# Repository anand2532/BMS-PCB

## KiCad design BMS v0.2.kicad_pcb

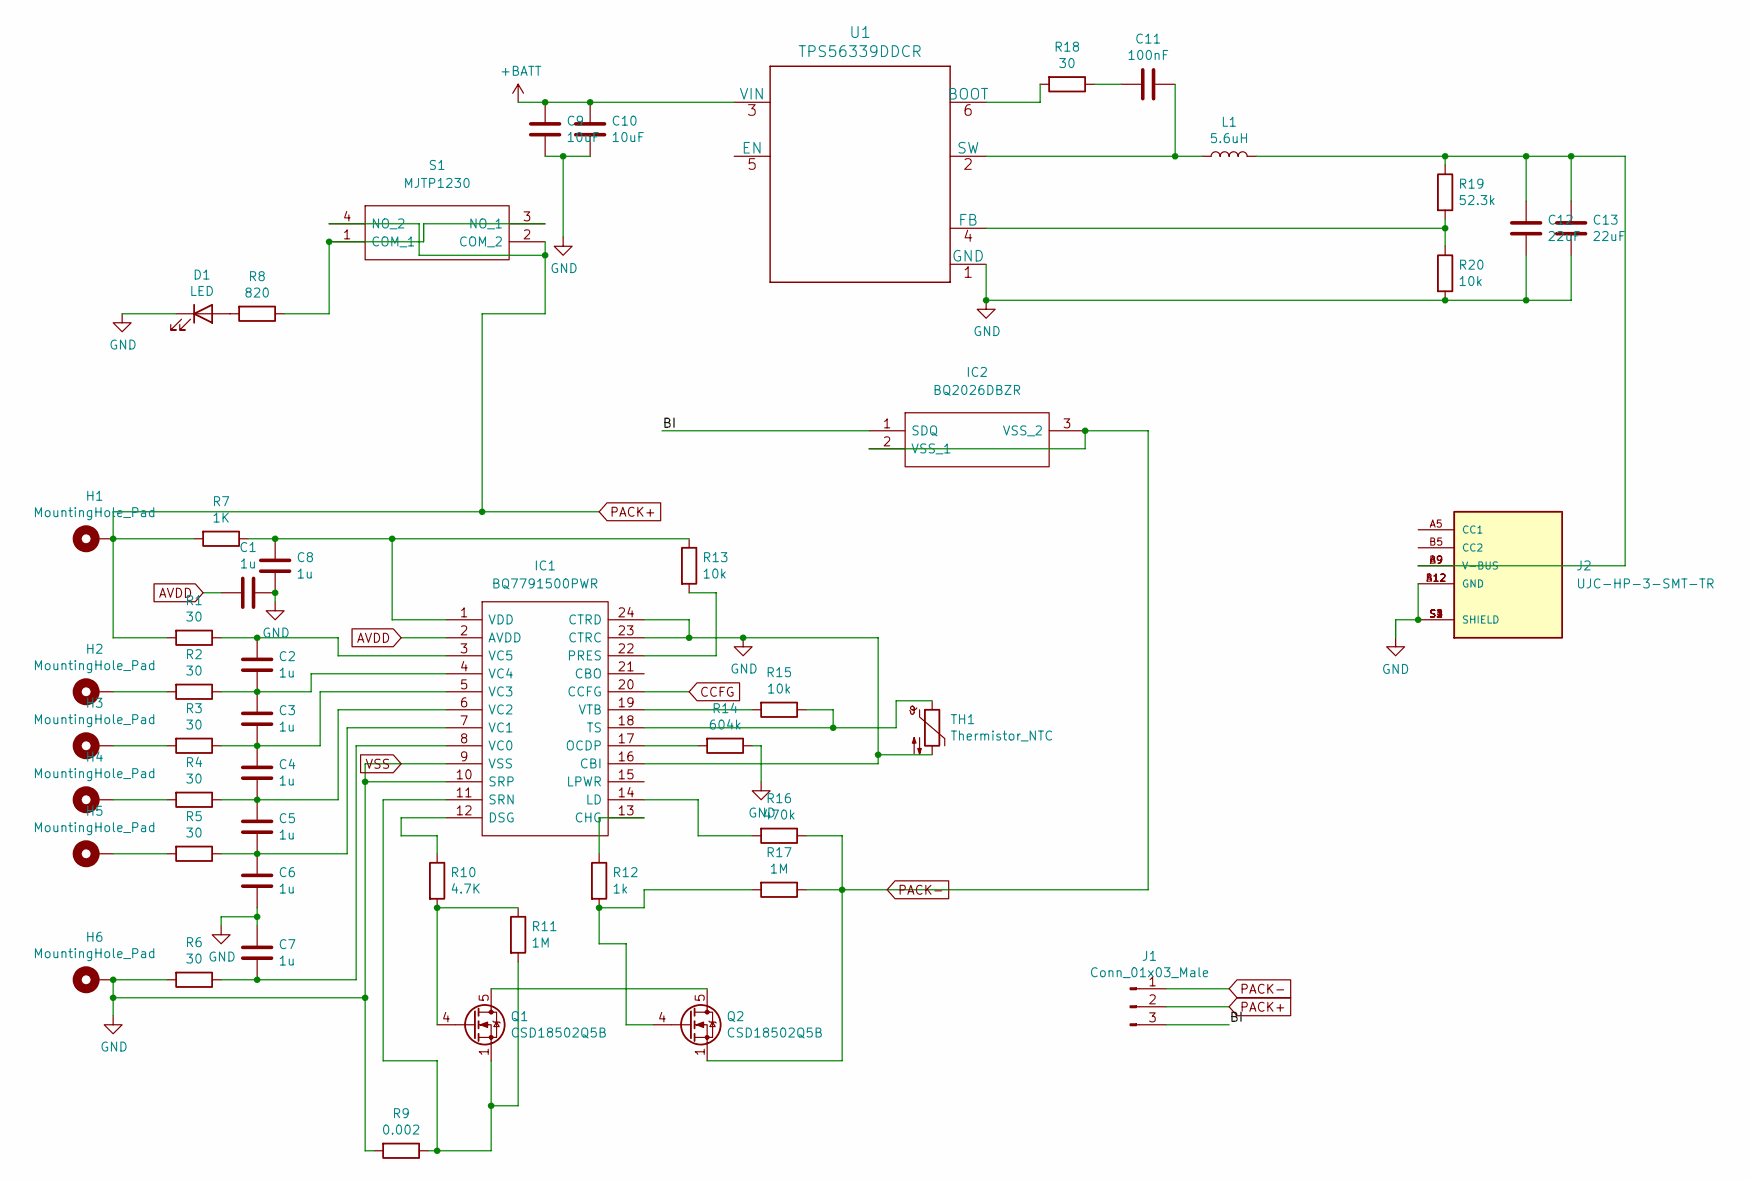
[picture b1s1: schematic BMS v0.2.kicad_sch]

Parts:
C1, C2, C3, C4, C5, C6, C7, C8: 1u; C_0603_1608Metric
C9, C10: 10uF; C_0805_2012Metric
C11: 100nF; C_0603_1608Metric
C12, C13: 22uF; C_0805_2012Metric
D1: LED; LED_0603_1608Metric
H1, H6: MountingHole_Pad; MountingHole_5.3mm_M5_Pad_Via
H2, H3, H4, H5: MountingHole_Pad; MountingHole_2.2mm_M2_Pad_Via
IC1: BQ7791500PWR; SOP65P640X120-24N; Manufacturer_Part_Number BQ7791500PWR; Mouser Part Number 595-BQ7791500PWR
IC2: BQ2026DBZR; SOT95P237X112-3N; Manufacturer_Part_Number BQ2026DBZR
J1: Conn_01x03_Male; MR30
J2: UJC-HP-3-SMT-TR; CUI_UJC-HP-3-SMT-TR; PARTREV 04/30/2020
L1: 5.6uH; IND_SRN8040TA-5R6M
Q1, Q2: CSD18502Q5B
R1, R2, R3, R4, R5, R6: 30; R_0805_2012Metric
R7: 1K; R_0805_2012Metric
R8: 820; LED_1206_3216Metric
R9: 0.002; R_2512_6332Metric
R10: 4.7K; R_0603_1608Metric
R11, R17: 1M; R_0603_1608Metric
R12: 1k; R_0603_1608Metric
R13, R15, R20: 10k; R_0603_1608Metric
R14: 604k; R_0603_1608Metric
R16: 470k; R_0603_1608Metric
R18: 30; R_0603_1608Metric
R19: 52.3k; R_0603_1608Metric
S1: MJTP1230; Switch_Tactile_THT_6x6mm_MJTP1230; Manufacturer_Part_Number MJTP1230; Mouser Part Number 642-MJTP1230
TH1: Thermistor_NTC; NTCLE101E3C90173
U1: TPS56339DDCR

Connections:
+BATT: C9.1, C10.1, U1.3 (VIN)
/BI: IC2.1 (SDQ), J1.3
AVDD: C1.2, IC1.2 (AVDD)
CCFG: IC1.20 (CCFG)
unnamed: C2.1, IC1.3 (VC5), R1.1
unnamed: C2.2, C3.1, IC1.4 (VC4), R2.1
unnamed: C3.2, C4.1, IC1.5 (VC3), R3.1
unnamed: C4.2, C5.1, IC1.6 (VC2), R4.1
unnamed: C5.2, C6.1, IC1.7 (VC1), R5.1
unnamed: C7.2, IC1.8 (VC0), R6.1
unnamed: C8.1, IC1.1 (VDD), R7.1, R13.1
unnamed: C11.1, L1.1, U1.2 (SW)
unnamed: C11.2, R18.1
unnamed: C12.1, C13.1, J2.A9 (V-BUS), J2.B9 (V-BUS), L1.2, R19.1
unnamed: D1.2 (A), R8.2
unnamed: H2.1, R2.2
unnamed: H3.1, R3.2
unnamed: H4.1, R4.2
unnamed: H5.1, R5.2
unnamed: IC1.11 (SRN), Q1.1 (S), Q1.2 (S), Q1.3 (S), R9.1, R11.2
unnamed: IC1.12 (DSG), R10.1
unnamed: IC1.13 (CHG), R12.1
unnamed: IC1.14 (LD), R16.2
unnamed: IC1.17 (OCDP), R14.2
unnamed: IC1.18 (TS), R15.1, TH1.1
unnamed: IC1.19 (VTB), R15.2
unnamed: IC1.22 (PRES), R13.2
unnamed: Q1.4 (G), R10.2, R11.1
unnamed: Q1.5 (D), Q2.5 (D)
unnamed: Q2.4 (G), R12.2, R17.2
unnamed: R8.1, S1.1 (COM_1), S1.3 (NO_1)
unnamed: R18.2, U1.6 (BOOT)
unnamed: R19.2, R20.1, U1.4 (FB)
PACK+: H1.1, J1.2, R1.2, R7.2, S1.2 (COM_2), S1.4 (NO_2)
PACK-: IC2.2 (VSS_1), IC2.3 (VSS_2), J1.1, Q2.1 (S), Q2.2 (S), Q2.3 (S), R16.1, R17.1
VSS: C1.1, C6.2, C7.1, C8.2, C9.2, C10.2, C12.2, C13.2, D1.1 (K), H6.1, IC1.9 (VSS), IC1.10 (SRP), IC1.16 (CBI), IC1.23 (CTRC), IC1.24 (CTRD), J2.A12 (GND), J2.B12 (GND), J2.S1 (SHIELD), J2.S2 (SHIELD), J2.S3 (SHIELD), J2.S4 (SHIELD), R6.2, R9.2, R14.1, R20.2, TH1.2, U1.1 (GND)

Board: 2 copper layers, 50 parts (30 on the bottom side), 35 nets, no tracks yet.

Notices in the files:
parts and their libraries:
Copyright 2021 Accelerated Designs. All rights reserved.
Copyright 2016 Accelerated Designs. All rights reserved.
